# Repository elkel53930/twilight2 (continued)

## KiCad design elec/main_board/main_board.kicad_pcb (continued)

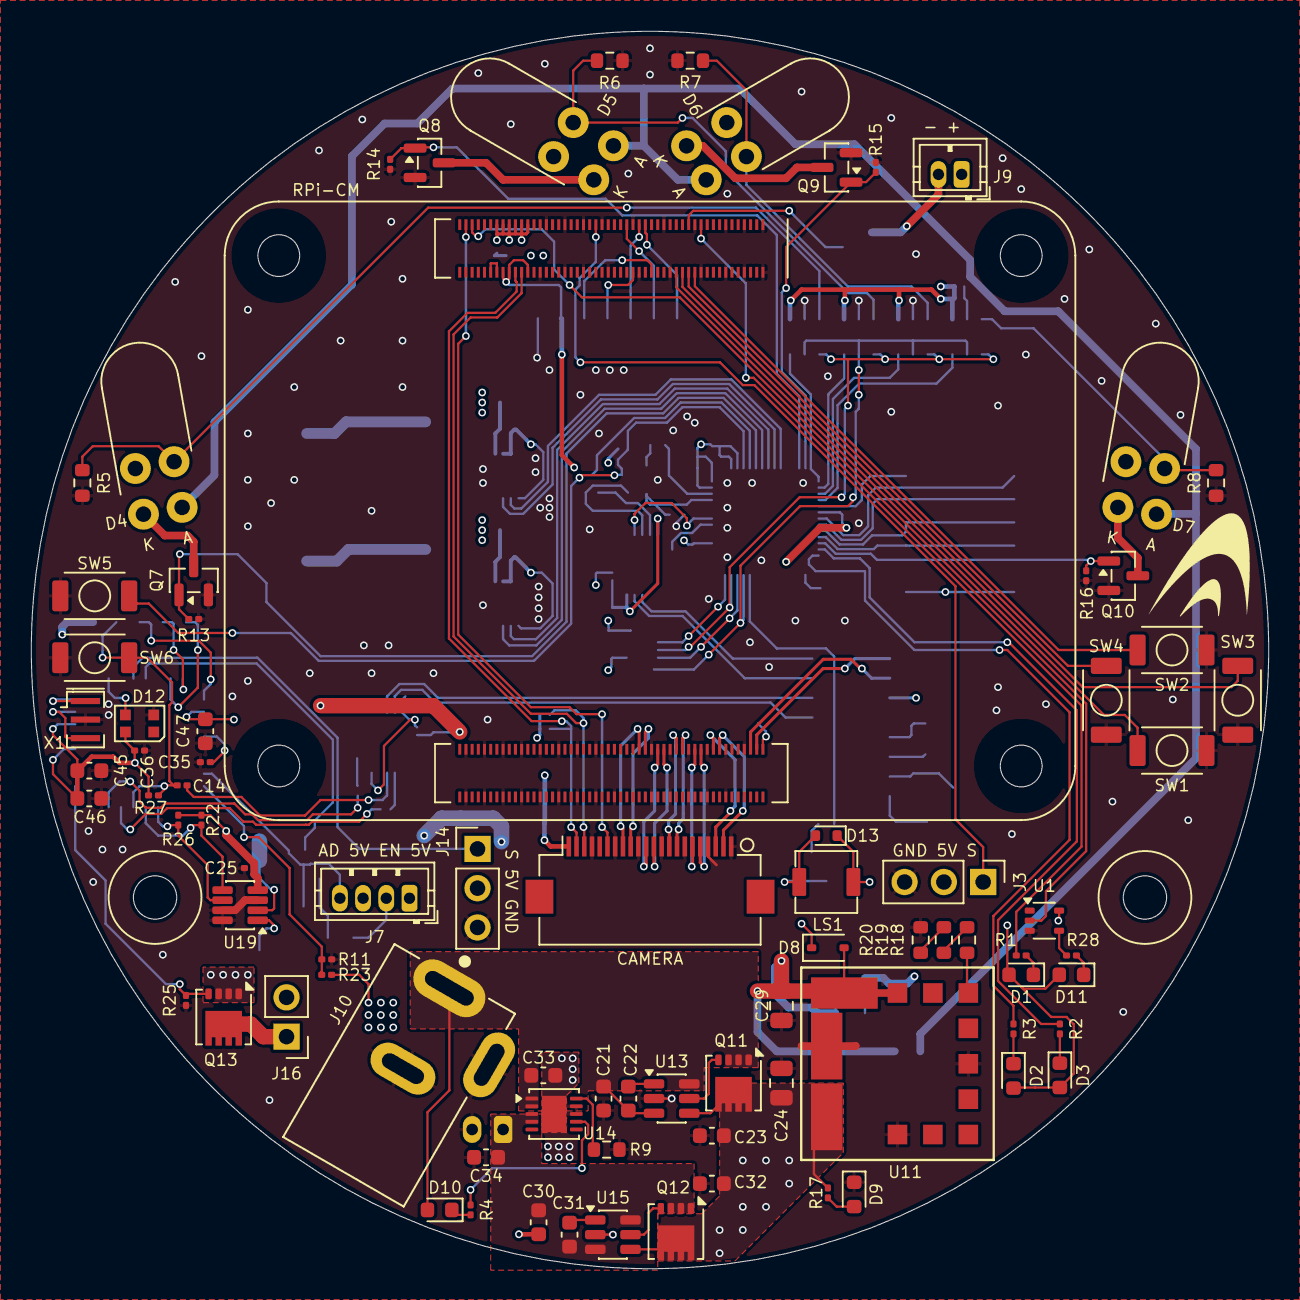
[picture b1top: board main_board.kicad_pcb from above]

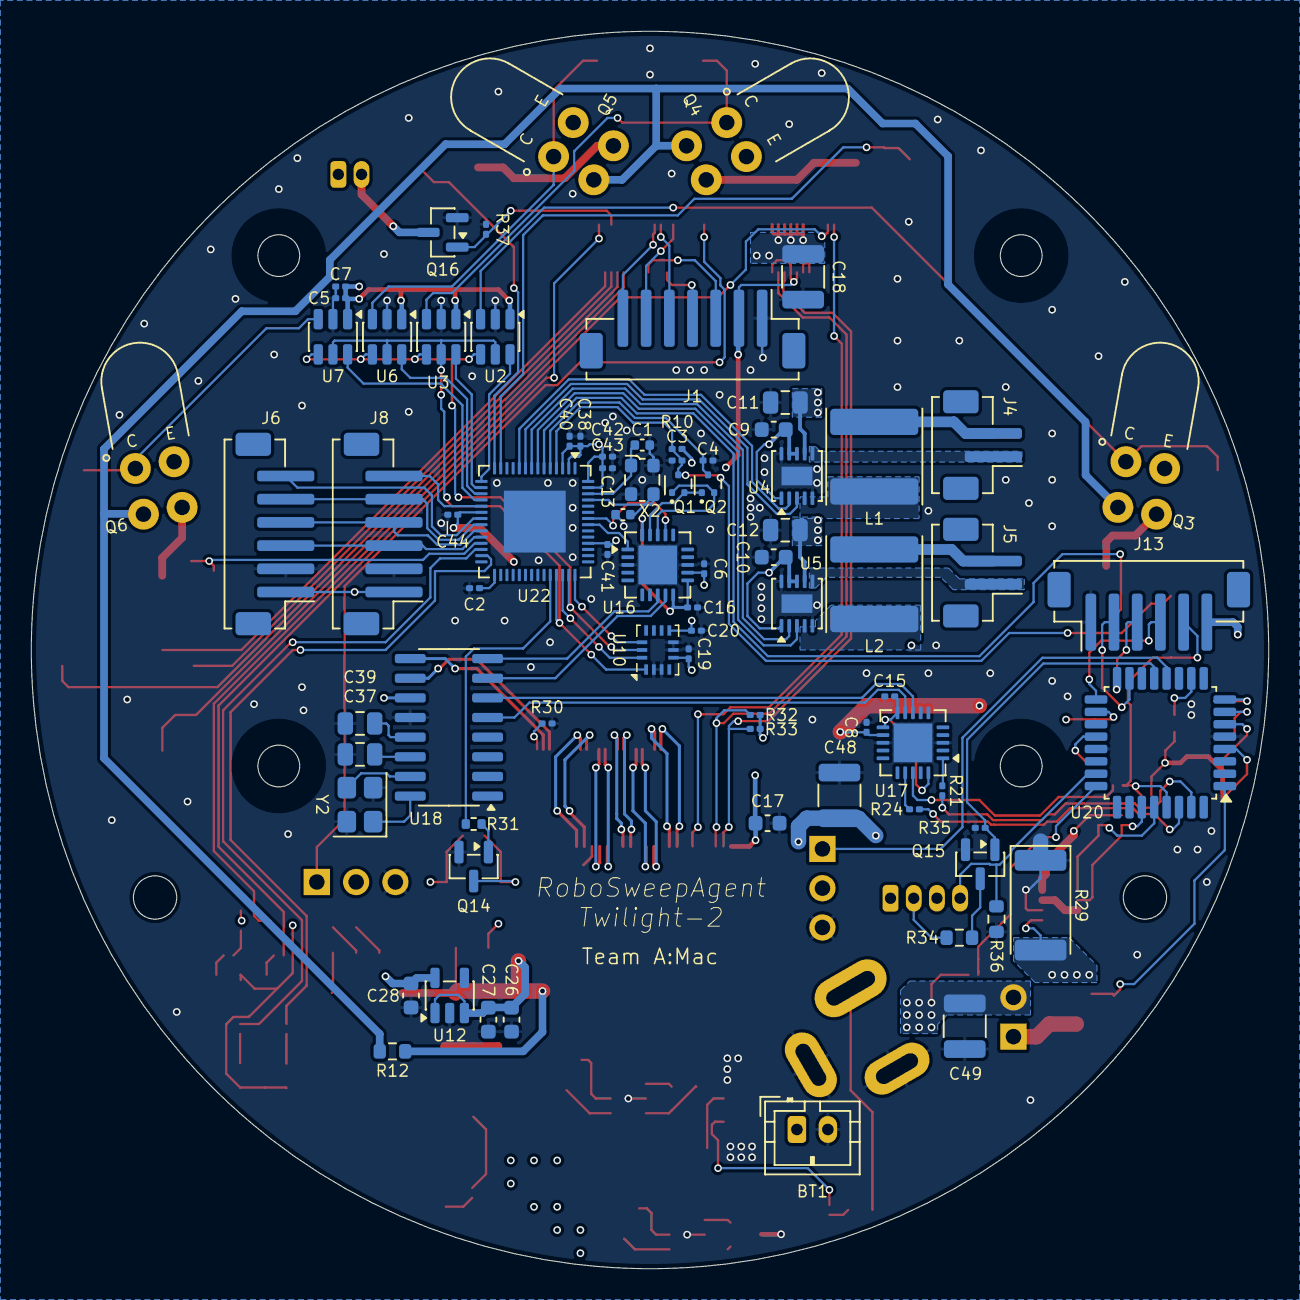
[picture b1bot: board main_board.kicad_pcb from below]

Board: 4 copper layers, 80.0 x 80.0 mm, 163 parts (78 on the bottom side), 138 nets.

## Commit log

2026-02-27 回路図作成、部品配置完了
2026-02-27 配線作業中
2026-03-01 アートワーク完了
2026-03-29 黄色検出コード
